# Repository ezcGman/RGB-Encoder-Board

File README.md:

# RGB Rotary Encoder

## v2 notes: What has changed?
I've added support for these awesome RGB Rotary Encoders, sold by "CN Futai Switches": https://www.aliexpress.com/item/1005002478550056.html
They have a PWM controllable LED inside the encoder, so we get **even more light**, just because we can :)
I also had to adjust some silk screening, including Adams logo, as I needed the space for the 2nd pin header :/ But I did my best to at least keep his logo and brand name!
There's also a 0805-size resistor on there now, as the switch either operates on 3v3, or on 5V with a current limiting resistor. You can basically pick whatever value you want, I picked 200R and it works nice. The higher resistance, the lower the brightness.

## What is this?
This is a super-overkill rotary encoder. Not only does it encode in a rotary fashion, it also lights up! It includes a ring of 20 ultra bright and even more ultra tiny Neopixel LEDs. Ever have trouble deciding between different LED colors? Well here you don't have to. Add this to your next project to give it a brilliant flare in whatever color, or combination of colors, you want.

## How do I use it?
Check out the example code in this repo. The provided examples are for use with a Teensy, but it can be used with any controller that can run Neopixels and read an encoder.

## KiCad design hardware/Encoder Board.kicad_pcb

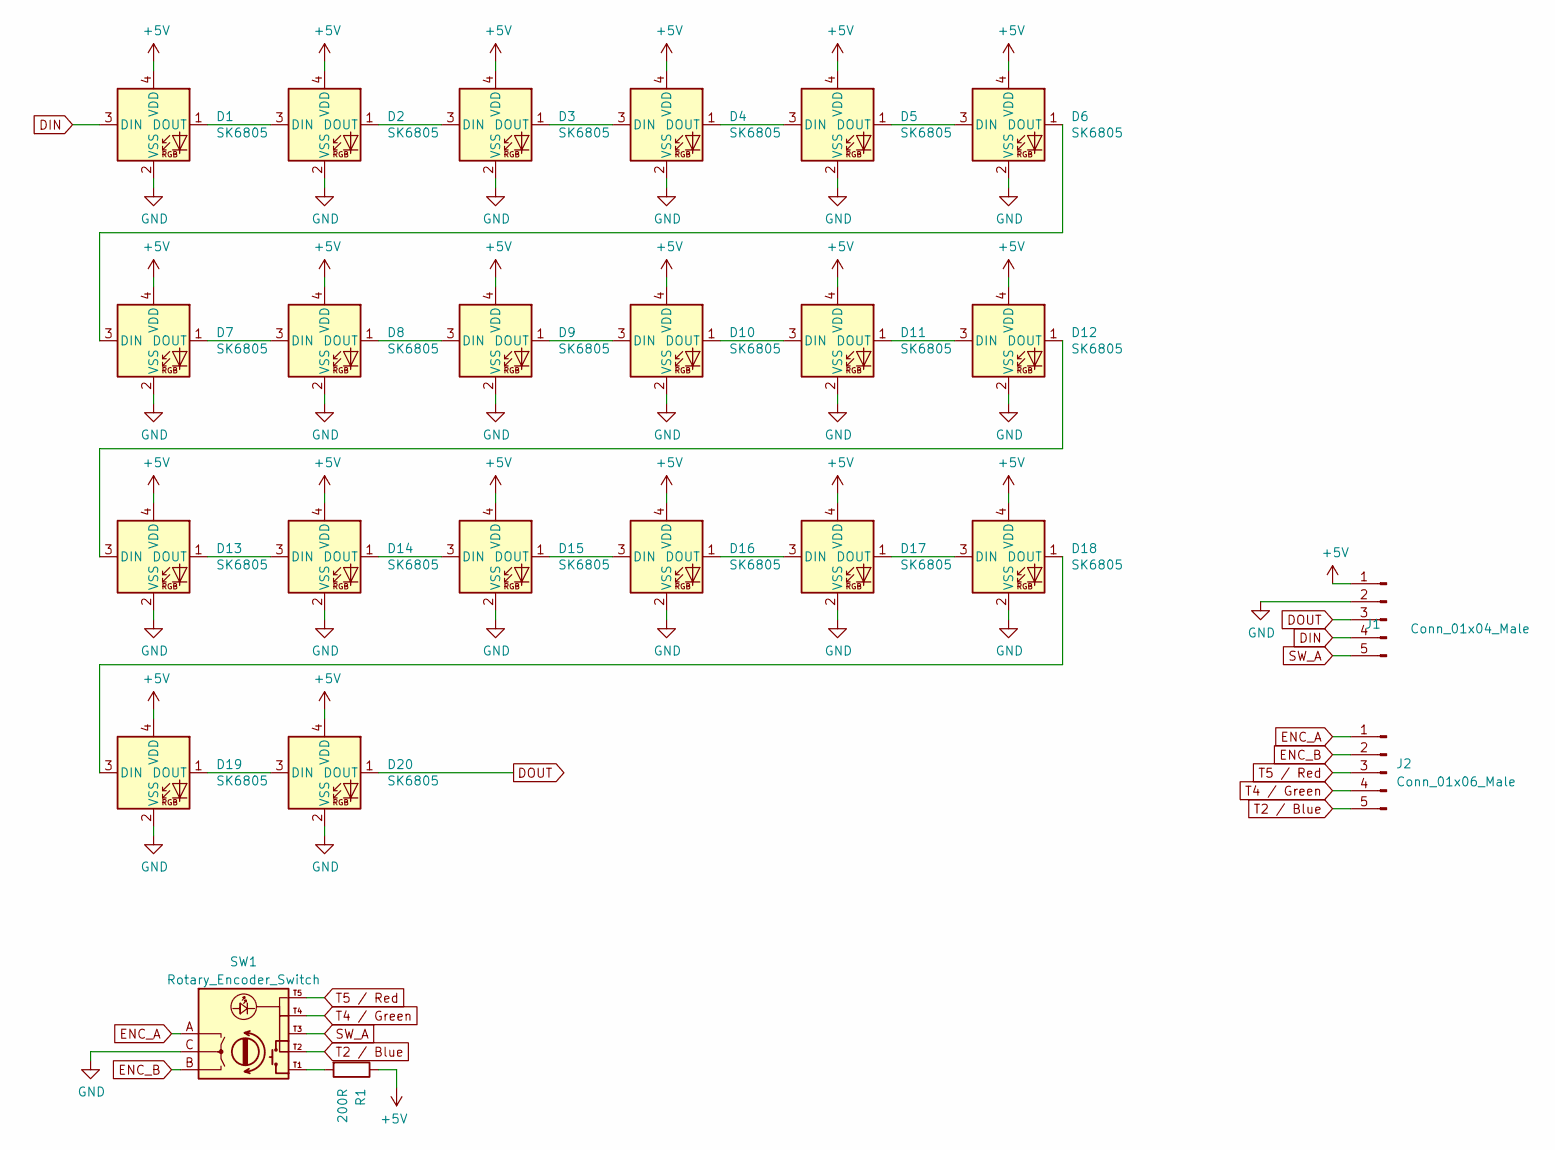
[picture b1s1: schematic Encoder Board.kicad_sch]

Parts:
D1, D2, D3, D4, D5, D6, D7, D8, D9, D10, D11, D12, D13, D14, D15, D16, D17, D18, D19, D20: SK6805; LED_SK6805_PLCC4_2.4x2.7mm_P1.3mm
J1: Conn_01x04_Male; PinHeader_1x05_P2.54mm_Vertical_SMD_Pin1Right
J2: Conn_01x06_Male; PinHeader_1x05_P2.54mm_Vertical_SMD_Pin1Left
R1: 200R; R_0805_2012Metric
SW1: Rotary_Encoder_Switch; LED_RotaryEncoder_Alps_EC12E-Switch_Vertical_H20mm

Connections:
+5V: D1.4 (VDD), D2.4 (VDD), D3.4 (VDD), D4.4 (VDD), D5.4 (VDD), D6.4 (VDD), D7.4 (VDD), D8.4 (VDD), D9.4 (VDD), D10.4 (VDD), D11.4 (VDD), D12.4 (VDD), D13.4 (VDD), D14.4 (VDD), D15.4 (VDD), D16.4 (VDD), D17.4 (VDD), D18.4 (VDD), D19.4 (VDD), D20.4 (VDD), J1.1, R1.1
DIN: D1.3 (DIN), J1.4
DOUT: D20.1 (DOUT), J1.3
ENC_A: J2.1, SW1.A
ENC_B: J2.2, SW1.B
GND: D1.2 (VSS), D2.2 (VSS), D3.2 (VSS), D4.2 (VSS), D5.2 (VSS), D6.2 (VSS), D7.2 (VSS), D8.2 (VSS), D9.2 (VSS), D10.2 (VSS), D11.2 (VSS), D12.2 (VSS), D13.2 (VSS), D14.2 (VSS), D15.2 (VSS), D16.2 (VSS), D17.2 (VSS), D18.2 (VSS), D19.2 (VSS), D20.2 (VSS), J1.2, SW1.C
unnamed: D1.1 (DOUT), D2.3 (DIN)
unnamed: D2.1 (DOUT), D3.3 (DIN)
unnamed: D3.1 (DOUT), D4.3 (DIN)
unnamed: D4.1 (DOUT), D5.3 (DIN)
unnamed: D5.1 (DOUT), D6.3 (DIN)
unnamed: D6.1 (DOUT), D7.3 (DIN)
unnamed: D7.1 (DOUT), D8.3 (DIN)
unnamed: D8.1 (DOUT), D9.3 (DIN)
unnamed: D10.1 (DOUT), D11.3 (DIN)
unnamed: D9.1 (DOUT), D10.3 (DIN)
unnamed: D11.1 (DOUT), D12.3 (DIN)
unnamed: D12.1 (DOUT), D13.3 (DIN)
unnamed: D13.1 (DOUT), D14.3 (DIN)
unnamed: D14.1 (DOUT), D15.3 (DIN)
unnamed: D15.1 (DOUT), D16.3 (DIN)
unnamed: D16.1 (DOUT), D17.3 (DIN)
unnamed: D17.1 (DOUT), D18.3 (DIN)
unnamed: D18.1 (DOUT), D19.3 (DIN)
unnamed: D19.1 (DOUT), D20.3 (DIN)
unnamed: R1.2, SW1.T1 (T1/COM)
SW_A: J1.5, SW1.T3 (T3/SW)
T2 / Blue: J2.5, SW1.T2
T4 / Green: J2.4, SW1.T4
T5 / Red: J2.3, SW1.T5

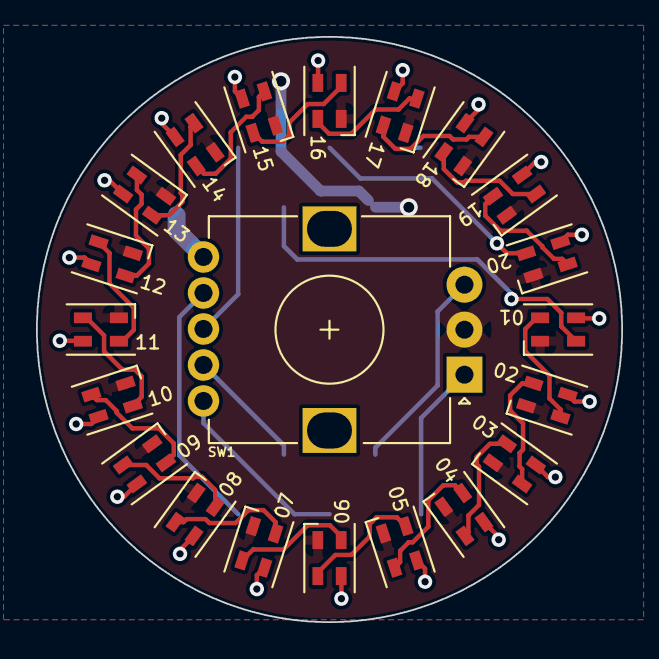
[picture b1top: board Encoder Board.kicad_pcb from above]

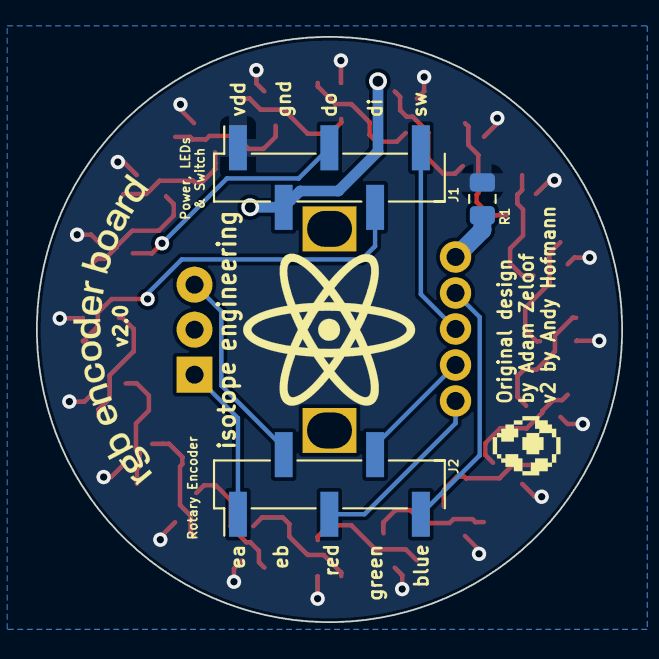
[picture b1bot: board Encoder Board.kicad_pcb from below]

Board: 2 copper layers, 32.5 x 32.5 mm, 24 parts (3 on the bottom side), 30 nets.

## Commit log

2021-12-27 First commit of v2, supporting RGB Encoders
2021-12-27 Added one missing therma relief
2021-12-27 Updated ReadMe for v2
2021-12-28 Fixed a few more silk screens
